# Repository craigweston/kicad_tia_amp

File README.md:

This is a Kicad project of a Termination Insensitive Amplifier based on the design by Wes Hayward, W7ZOI, and Bob Kopski, K3NHI.

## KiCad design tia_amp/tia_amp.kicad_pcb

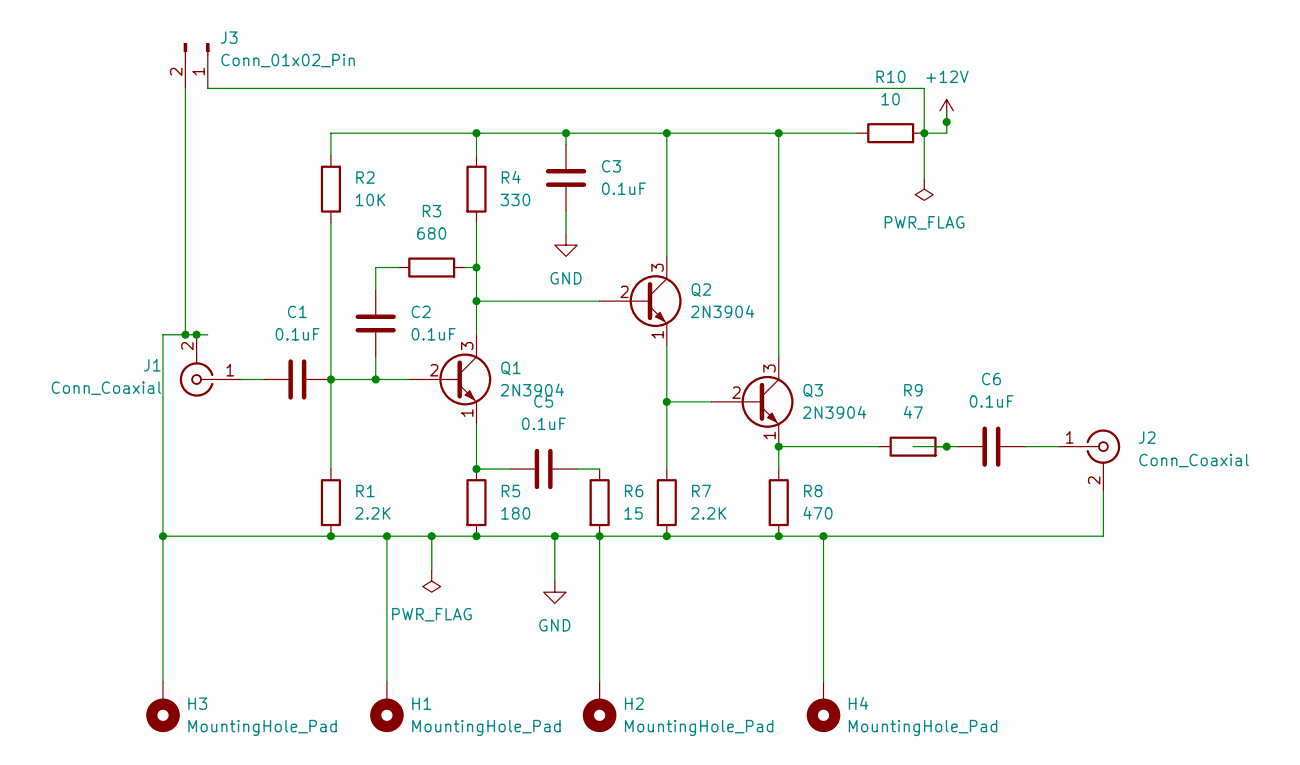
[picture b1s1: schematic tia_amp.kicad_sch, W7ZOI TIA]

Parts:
C1, C2, C3, C5, C6: 0.1uF; C_Disc_D3.8mm_W2.6mm_P2.50mm
H1, H2, H3, H4: MountingHole_Pad; MountingHole_2.2mm_M2_Pad_Via
J1, J2: Conn_Coaxial; SMA_Amphenol_132289_EdgeMount
J3: Conn_01x02_Pin; PinHeader_1x02_P2.54mm_Vertical
Q1, Q2, Q3: 2N3904; TO-92_Inline
R1, R7: 2.2K; R_Axial_DIN0207_L6.3mm_D2.5mm_P2.54mm_Vertical
R2: 10K; R_Axial_DIN0207_L6.3mm_D2.5mm_P2.54mm_Vertical
R3: 680; R_Axial_DIN0207_L6.3mm_D2.5mm_P2.54mm_Vertical
R4: 330; R_Axial_DIN0207_L6.3mm_D2.5mm_P2.54mm_Vertical
R5: 180; R_Axial_DIN0207_L6.3mm_D2.5mm_P2.54mm_Vertical
R6: 15; R_Axial_DIN0207_L6.3mm_D2.5mm_P2.54mm_Vertical
R8: 470; R_Axial_DIN0207_L6.3mm_D2.5mm_P2.54mm_Vertical
R9: 47; R_Axial_DIN0207_L6.3mm_D2.5mm_P2.54mm_Vertical
R10: 10; R_Axial_DIN0207_L6.3mm_D2.5mm_P2.54mm_Vertical

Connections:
+12V: J3.1, R10.2
GND: C3.2, H1.1, H2.1, H3.1, H4.1, J1.2 (Ext), J2.2 (Ext), J3.2, R1.2, R5.2, R6.2, R7.2, R8.2
unnamed: C2.1, R3.1
unnamed: C5.2, R6.1
unnamed: C6.1, R9.2
unnamed: C1.1, J1.1 (In)
unnamed: C6.2, J2.1 (In)
unnamed: C1.2, C2.2, Q1.2 (B), R1.1, R2.1
unnamed: Q1.3 (C), Q2.2 (B), R3.2, R4.2
unnamed: C5.1, Q1.1 (E), R5.1
unnamed: C3.1, Q2.3 (C), Q3.3 (C), R2.2, R4.1, R10.1
unnamed: Q2.1 (E), Q3.2 (B), R7.1
unnamed: Q3.1 (E), R8.1, R9.1

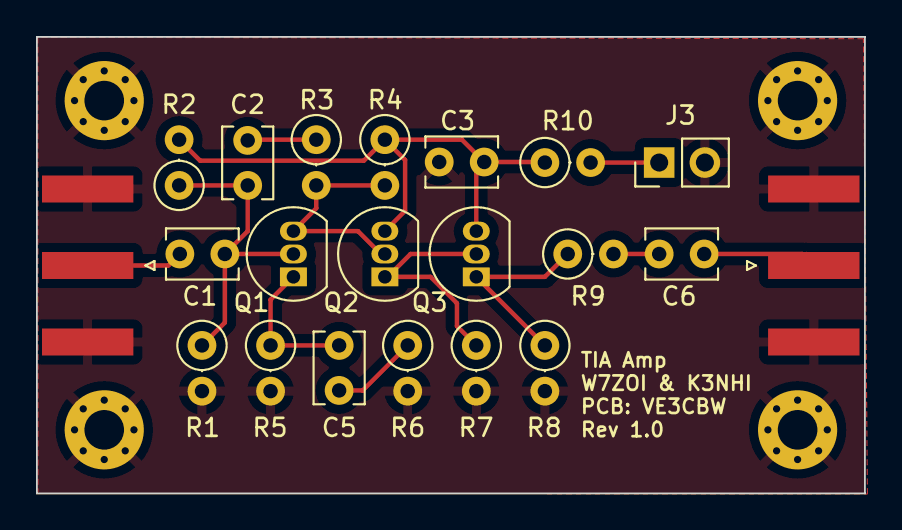
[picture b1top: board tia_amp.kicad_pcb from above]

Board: 2 copper layers, 46.0 x 25.4 mm, 25 parts (0 on the bottom side), 13 nets.

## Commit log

2024-11-16 ltspice
